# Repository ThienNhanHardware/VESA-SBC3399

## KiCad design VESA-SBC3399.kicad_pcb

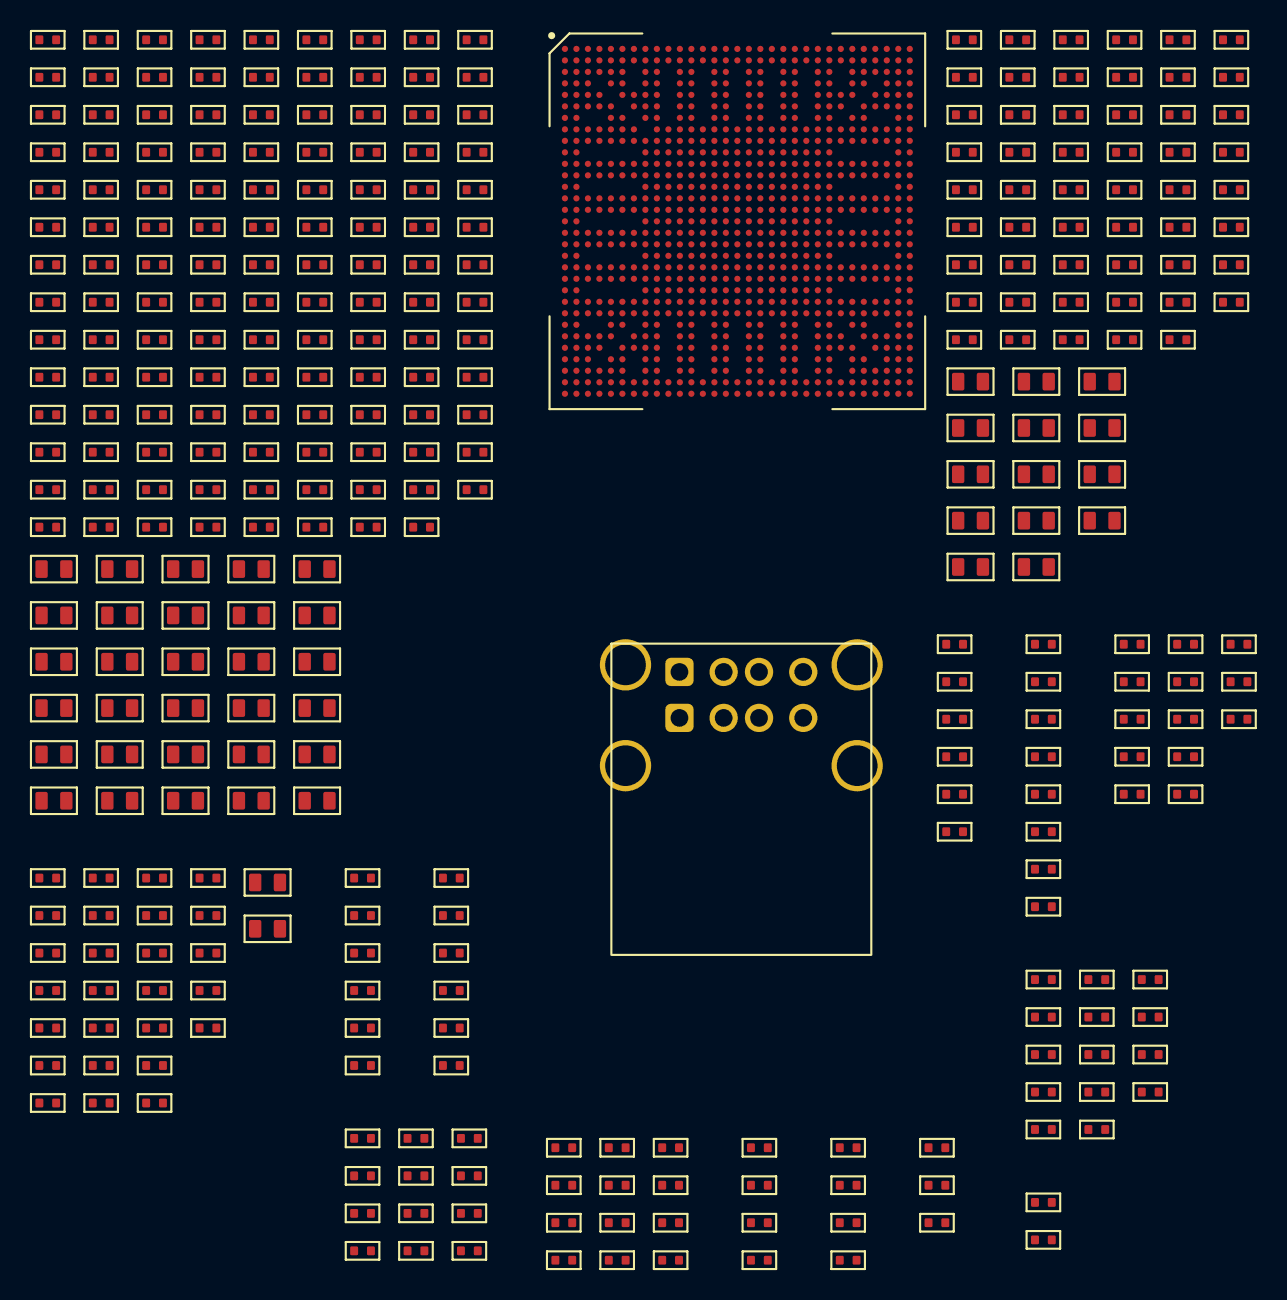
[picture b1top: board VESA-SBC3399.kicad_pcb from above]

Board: 2 copper layers, 342 parts (0 on the bottom side), 118 nets, no tracks yet.

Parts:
C2, C4, C7, C8, C9, C10, C14, C15, C16, C21, C23, C24, C28, C29, C30, C31, C32, C33, C34, C37, C38, C40, C41, C42, C47, C50, C51, C52, C53, C54, C56, C57, C58, C61, C62, C63, C67, C68, C69, C72, C73, C77, C78, C79, C80, C81, C82, C83, C84, C88, C89, C90, C91, C92, C94, C95, C98, C99, C100, C101, C102, C104, C105, C106, C107, C108, C109, C110, C111, C113, C114, C115, C116, C117, C118, C119, C122, C123, C124, C126, C127, C128, C129, C130, C131, C132, C136, C137, C138, C139, C140, C141, C142, C143, C146, C147, C148, C149, C150, C151, C152, C156, C157, C158, C159, C160, C161, C162, C163, C168, C170, C171, C172, C173, C174, C175, C176, C178, C179, C180, C181, C182, C183, C184, C185, C186, C187, C188, C189, C190, C191, C192, C193, C194, C195, C196, C197, C198, C199, C200, C201, C202, C203, C204, C205, C206, C207, C209, C210, C211, C212, C213, C214, C215, C216, C218, C219, C220, C221, C222, C223, C224, C225, C226, C227, C228, C229, C230, C231, C232, C233, C234, C235, C236, C237, C238, C239, C240, C241, C242, C243, C244, C245, C246, C247, C248: CAPC1005X50N
C13, C17, C18, C19, C20, C39, C43, C44, C45, C46, C49, C59, C60, C64, C65, C66, C70, C71, C74, C85, C86, C87, C93, C96, C97, C103, C112, C120, C121, C125, C133, C134, C135, C144, C145, C153, C154, C155, C164, C165, C166, C167, C169, C177, C208, C217: CAPC1608X80N
CON1: AF SS-JB17.6
R1, R2, R4, R5, R7, R9, R11, R12, R13, R14, R15, R17, R18, R21, R22, R23, R24, R25, R26, R27, R28, R29, R30, R31, R32, R33, R34, R35, R36, R37, R39, R40, R41, R43, R44, R45, R46, R47, R48, R50, R51, R52, R53, R55, R56, R57, R60, R61, R62, R63, R64, R65, R66, R67, R68, R69, R70, R71, R72, R73, R74, R75, R76, R77, R78, R79, R80, R81, R82, R83, R84, R85, R86, R87, R88, R89, R90, R93, R94, R95, R96, R97, R98, R99, R100, R101, R102, R103, R104, R105, R106, R107, R108, R109, R110, R111, R112, R113, R114, R115, R116, R117, R118, R119, R120, R121, R122, R123: RESC1005X35N
U11: RK3399; BGA828C65P31X31_2100X2100X161

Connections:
+0V9_AVCC: C108.1, C109.1, C110.1, C185.1, C186.1, C202.1, C204.1, C228.1, C231.1, C232.1, C233.1, C238.1, U11.H14 (DDR1PLL_AVDD_0V9), U11.L24 (EMMC_COREDLL_0V9), U11.R8 (DDR0PLL_AVDD_0V9), U11.R17 (PLL_AVDD_0V9), U11.T24 (PMU_VDD_0V9), U11.W24 (PCIE_AVDD_0V9), U11.Y18 (TYPEC0_AVDD_0V9_2), U11.Y19 (TYPEC0_AVDD_0V9_1), U11.Y21 (TYPEC1_AVDD_0V9_1), U11.Y22 (TYPEC1_AVDD_0V9_2)
+0V9_AVCC_HDMI: C96.1, U11.AA16 (HDMI_AVDD_0V9_1), U11.AA17 (HDMI_AVDD_0V9_2)
+0V9_VDD_CENTER: C70.1, C71.1, C72.1, C168.1, C169.1, C170.1, C171.1, C172.1, C173.1, C174.1, C175.1, R36.1, U11.M11 (CENTERLOGIC_VDD_1), U11.M12 (CENTERLOGIC_VDD_2), U11.M13 (CENTERLOGIC_VDD_3), U11.M14 (CENTERLOGIC_VDD_4), U11.M15 (CENTERLOGIC_VDD_5), U11.N11 (CENTERLOGIC_VDD_6), U11.N12 (CENTERLOGIC_VDD_7), U11.P13 (CENTERLOGIC_VDD_8), U11.P14 (CENTERLOGIC_VDD_9), U11.P15 (CENTERLOGIC_VDD_10)
+0V9_VDD_CPU_B: C15.1, C16.1, C17.1, C18.1, C19.1, C20.1, C132.1, C133.1, C134.1, C135.1, C136.1, C137.1, C138.1, C139.1, C140.1, C141.1, C142.1, R13.2, U11.K19 (BIGCPU_VDD_12), U11.K21 (BIGCPU_VDD_13), U11.L18 (BIGCPU_VDD_8), U11.L19 (BIGCPU_VDD_1), U11.L21 (BIGCPU_VDD_2), U11.L23 (BIGCPU_VDD_11), U11.M18 (BIGCPU_VDD_3), U11.M19 (BIGCPU_VDD_4), U11.M20 (BIGCPU_VDD_5), U11.M21 (BIGCPU_VDD_6), U11.M22 (BIGCPU_VDD_7), U11.N20 (BIGCPU_VDD_10), U11.N22 (BIGCPU_VDD_9)
+0V9_VDD_CPU_L: C86.1, C87.1, C88.1, C143.1, C144.1, C145.1, C146.1, C147.1, C148.1, C149.1, C150.1, C151.1, R39.1, U11.P20 (LITCPU_VDD_1), U11.P22 (LITCPU_VDD_4), U11.R19 (LITCPU_VDD_2), U11.R20 (LITCPU_VDD_3), U11.R22 (LITCPU_VDD_7), U11.T20 (LITCPU_VDD_6), U11.T22 (LITCPU_VDD_5)
+0V9_VDD_GPU: C41.1, C42.1, C43.1, C44.1, C45.1, C46.1, C152.1, C153.1, C154.1, C155.1, C156.1, C157.1, C158.1, C159.1, C160.1, C161.1, C162.1, C163.1, C164.1, C165.1, C166.1, C167.1, R26.2, U11.R11 (GPU_VDD_8), U11.R12 (GPU_VDD_9), U11.R13 (GPU_VDD_13), U11.T11 (GPU_VDD_10), U11.T12 (GPU_VDD_11), U11.T13 (GPU_VDD_12), U11.T14 (GPU_VDD_14), U11.U13 (GPU_VDD_7), U11.V11 (GPU_VDD_15), U11.V12 (GPU_VDD_16), U11.V13 (GPU_VDD_6), U11.V14 (GPU_VDD_5), U11.V15 (GPU_VDD_4), U11.V16 (GPU_VDD_17), U11.W10 (GPU_VDD_20), U11.W11 (GPU_VDD_1), U11.W12 (GPU_VDD_2), U11.W14 (GPU_VDD_3), U11.W15 (GPU_VDD_19), U11.W16 (GPU_VDD_18)
+0V9_VDD_LOG: C123.1, C124.1, C125.1, C128.1, C176.1, C177.1, C178.1, C179.1, C180.1, C181.1, C182.1, C183.1, C184.1, R50.1, R50.2, R53.1, U11.L17 (LOGIC_VDD_10), U11.M17 (LOGIC_VDD_9), U11.T17 (LOGIC_VDD_11), U11.U17 (LOGIC_VDD_8), U11.U18 (LOGIC_VDD_7), U11.U20 (LOGIC_VDD_12), U11.V18 (LOGIC_VDD_5), U11.V19 (LOGIC_VDD_4), U11.V20 (LOGIC_VDD_3), U11.V21 (LOGIC_VDD_2), U11.V22 (LOGIC_VDD_1), U11.W20 (LOGIC_VDD_6)
+1V5_VCC: C101.1, C196.1, R61.1, U11.AC8 (APIO4_VDDPST)
+1V8_AVCC: C94.1, C187.1, C188.1, C189.1, C234.1, C235.1, C239.1, C242.1, C244.1, C245.1, R67.1, R93.1, R95.1, U11.AA18 (TYPEC0_AVDD_1V8), U11.AA21 (TYPEC1_AVDD_1V8), U11.AC24 (ADC_AVDD), U11.P18 (PLL_AVDD_1V8), U11.R24 (PMUIO1_VDD_1V8), U11.U25 (PMU_VDD_1V8)
+1V8_AVCC_HDMI: C93.1, C246.1, C247.1, U11.AD16 (HDMI_AVDD_1V8)
+1V8_VCC: C73.1, C74.1, C115.1, C190.1, C192.1, C193.1, C194.1, C203.1, C205.1, R14.1, R27.1, R46.1, R47.1, R52.1, R60.1, R118.1, R119.1, R120.1, R121.1, R122.1, R123.1, U11.AA8 (APIO5_VDDPST), U11.AB8 (APIO3_VDD_1V8), U11.J22 (APIO1_VDDPST), U11.K24 (EMMC_VDD_1V8), U11.N23 (PMUIO2_VDDPST), U11.P23 (PMUIO2_VDD), U11.Y8 (APIO5_VDD), U11.Y24 (PCIE_AVDD_1V8)
+1V8_VCC_EFUSE: C201.1, R66.1, U11.AD23 (EFUSE)
+1V35_VCC_DDR: C82.1, C83.1, C84.1, C85.1, C208.1, C209.1, C210.1, C211.1, C212.1, C213.1, C214.1, C215.1, C216.1, C217.1, C218.1, C219.1, C220.1, C221.1, C222.1, C223.1, C224.1, C225.1, C226.1, C229.1, R37.1, R85.1, R86.1, U11.J11 (DDR1_VDD_1), U11.J12 (DDR1_VDD_2), U11.J13 (DDR1_VDD_3), U11.J14 (DDR1_VDD_4), U11.J15 (DDR1_VDD_5), U11.J16 (DDR1_VDD_6), U11.J17 (DDR1_VDD_7), U11.J18 (DDR1_VDD_8), U11.K11 (DDR1_VDD_9), U11.K13 (DDR1_VDD_10), U11.K15 (DDR1_VDD_11), U11.K17 (DDR1_VDD_12), U11.L9 (DDR0_VDD_1), U11.L10 (DDR0_VDD_2), U11.M9 (DDR0_VDD_3), U11.N9 (DDR0_VDD_4), U11.N10 (DDR0_VDD_5), U11.P9 (DDR0_VDD_6), U11.R9 (DDR0_VDD_7), U11.R10 (DDR0_VDD_8), U11.T9 (DDR0_VDD_9), U11.U9 (DDR0_VDD_10), U11.U10 (DDR0_VDD_11), U11.V9 (DDR0_VDD_12)
+1V35_VCC_DDR0_CLK: C227.1, R85.2, U11.M7 (DDR0_CLK_VDD)
+1V35_VCC_DDR1_CLK: C230.1, R86.2, U11.G12 (DDR1_CLK_VDD)
+3V0_IOVCC_SD: C97.1, C206.1, U11.T23 (SDMMC0_VDD)
+3V0_SDMMC0_VDDPST: C207.1, U11.U26 (SDMMC0_VDDPST)
+3V0_VCC: C103.1, C195.1, U11.AC9 (APIO4_VDD)
+3V0_VCC_RTC: C113.1, C114.1, R43.1, R48.1
+3V0_VCC_SD: C79.1, C80.1, C81.1
+3V3_VCC_LAN: C191.1, R107.1, R108.1, R109.1, R110.1, R111.1, U11.J23 (APIO1_VDD)
+3V3_VCC_SYS: C62.1, C63.1, C64.1, C65.1, C66.1, C77.1, C78.1, C106.1, C107.1, C111.1, C236.1, C237.1, C240.1, R33.1, R41.1, U11.AB18 (TYPEC0_AVDD_3V3), U11.AB21 (TYPEC1_AVDD_3V3), U11.Y25 (USB_AVDD_3V3)
+5V0_SYS: C13.1, C14.1, C39.1, C40.1, C52.1, C53.1, C54.1, C59.1, C60.1, C61.1, C68.1, C69.1, C90.1, C92.1, C95.1, C98.1, C100.1, C102.1, C120.1, C121.1, C122.1, R29.1
+5V0_USB: C32.1, C33.1, C34.1
+5V0_VBUS_USBA0: C2.1, CON1.1 (VBUS1)
+5V0_VBUS_USBA1: C4.1, CON1.5 (VBUS2)
+12V_SYS: C8.1, C9.1, C10.1, C28.1, C29.1, C30.1, C31.1, C49.1, C50.1, R7.1, R28.1
/0V9_VDD_CPU_B_FB: R13.1, U11.N18 (BIGCPU_VDD_COM)
/0V9_VDD_GPU_FB: R26.1, U11.T15 (GPU_VDD_COM)
/BT_REG_ON: R67.2, R68.1, U11.V30 (GPIO0_B1/PMUIO2_VOLSEL)
/CPU-RK3399/CPU-RK3399 HDMI/HDMI_TMDS0_R+: R98.1, U11.AK17 (HDMI_TX0P)
/CPU-RK3399/CPU-RK3399 HDMI/HDMI_TMDS0_R-: R99.1, U11.AL17 (HDMI_TX0N)
/CPU-RK3399/CPU-RK3399 HDMI/HDMI_TMDS1_R+: R100.1, U11.AK18 (HDMI_TX1P)
/CPU-RK3399/CPU-RK3399 HDMI/HDMI_TMDS1_R-: R101.1, U11.AL18 (HDMI_TX1N)
/CPU-RK3399/CPU-RK3399 HDMI/HDMI_TMDS2_R+: R103.1, U11.AK19 (HDMI_TX2P)
/CPU-RK3399/CPU-RK3399 HDMI/HDMI_TMDS2_R-: R104.1, U11.AL19 (HDMI_TX2N)
/CPU-RK3399/CPU-RK3399 HDMI/HDMI_TMDS_CLK_R+: R97.1, U11.AK16 (HDMI_TCP)
/CPU-RK3399/CPU-RK3399 HDMI/HDMI_TMDS_CLK_R-: R102.1, U11.AL16 (HDMI_TCN)
/CPU-RK3399/CPU-RK3399 PMU Controller/CPU_SYS_CLK32K_IN: C199.1, R62.1, U11.U31 (GPIO0_A0/TEST_CLKOUT0/CLK32K_IN)
/CPU-RK3399/CPU-RK3399 PMU Controller/CPU_XIN_OSC: C198.1, R63.1, U11.Y31 (XIN_OSC)
/CPU-RK3399/CPU-RK3399 PMU Controller/CPU_XOUT_OSC: R63.2, R64.2, U11.Y30 (XOUT_OSC)
/CPU-RK3399/CPU-RK3399 Protocols/CPU_I2C0_SCL: R122.2, U11.N30 (GPIO1_C0/SPI3_TXD/I2C0_SCL)
/CPU-RK3399/CPU-RK3399 Protocols/CPU_I2C0_SDA: R123.2, U11.M26 (GPIO1_B7/SPI3_RXD/I2C0_SDA)
/CPU-RK3399/CPU-RK3399 Protocols/CPU_I2C3_SCL: R119.2, U11.AL2 (GPIO4_C1/I2C3_SCL/UART2B_TX)
/CPU-RK3399/CPU-RK3399 Protocols/CPU_I2C3_SDA: R118.2, U11.AG6 (GPIO4_C0/I2C3_SDA/UART2B_RX)
/CPU-RK3399/CPU-RK3399 Protocols/CPU_I2C4_SCL: R120.2, U11.P30 (GPIO1_B4/I2C4_SCL)
/CPU-RK3399/CPU-RK3399 Protocols/CPU_I2C4_SDA: R121.2, U11.P31 (GPIO1_B3/I2C4_SDA)
/CPU-RK3399/CPU-RK3399 SAR-ADC/CPU_SYS_RAM_ID: C241.1, R93.2, R94.1, U11.AG28 (ADC_IN3)
/CPU_SYS_RECOVERY: C243.1, R95.2, R96.2, U11.AH26 (ADC_IN1)
/CPU_SYS_RESET#: C119.1, C197.1, R47.2, U11.T30 (NPOR)
/PHY_CLKOUT: C248.1, R117.2
/PHY_MDIO: R107.2, U11.G26 (GPIO3_B5/MAC_MDIO/UART1_TX)
/PHY_TXD0: R111.2, R112.2
/PHY_TXD1: R110.2, R113.2
/PHY_TXD2: R109.2, R114.2
/PHY_TXD3: R108.2, R115.2
/PMIC_PWR_KEY#: C130.1, R48.2, U11.V27 (GPIO0_A5/EMMC_PWRON)
/PMIC_RTC_CLKO_CPU: R46.2, R62.2
/Power/0V9_VDD_CPU_B_PWR_EN: C23.1, R14.2
/Power/0V9_VDD_GPU_PWR_EN: C51.1, R27.2
/Power/0V9_VDD_LOG_FB: C128.2, R53.2, R55.2, R57.1
/Power/1V35_VCC_DDR_FB: C82.2, R40.1
/Power/3V3_VCC_SYS_FB: R33.2, R34.1
/Power/3V3_VCC_SYS_PWR_EN: C67.1, R35.2
/Power/5V0_SYS_FB: R29.2, R31.1
/Power/5V0_SYS_PWR_EN: R18.2, R28.2, R30.1
/Power/5V0_USB_PWR_EN: R17.2, R21.1
/Power/12V_SYS_OVLO: R9.2, R15.1
/Power/12V_SYS_PG: R12.2, R17.1, R18.1
/USB 2.0 Type-A/USBA0_D_R+: CON1.3 (D1+), R1.2
/USB 2.0 Type-A/USBA0_D_R-: CON1.2 (D1-), R2.2
/USB 2.0 Type-A/USBA1_D_R+: CON1.7 (D2+), R4.2
/USB 2.0 Type-A/USBA1_D_R-: CON1.6 (D2-), R5.2
/USBA0_D+: R1.1, U11.AB30 (USB0_DP)
/USBA0_D-: R2.1, U11.AB31 (USB0_DN)
/USBA1_D+: R4.1, U11.AA30 (USB1_DP)
/USBA1_D-: R5.1, U11.AA31 (USB1_DN)
CHGND: CON1.9 (SHIELD), CON1.10 (SHIELD), CON1.11 (SHIELD), CON1.12 (SHIELD)
GND: C2.2, C4.2, C7.2, C8.2, C9.2, C10.2, C13.2, C14.2, C15.2, C16.2, C17.2, C18.2, C19.2, C20.2, C21.2, C23.2, C28.2, C29.2, C30.2, C31.2, C32.2, C33.2, C34.2, C37.2, C38.2, C39.2, C40.2, C41.2, C42.2, C43.2, C44.2, C45.2, C46.2, C49.2, C50.2, C51.2, C52.2, C53.2, C54.2, C56.2, C57.2, C59.2, C60.2, C61.2, C62.2, C63.2, C64.2, C65.2, C66.2, C67.2, C68.2, C69.2, C70.2, C71.2, C72.2, C73.2, C74.2, C77.2, C78.2, C79.2, C80.2, C81.2, C83.2, C84.2, C85.2, C86.2, C87.2, C88.2, C89.2, C90.2, C91.2, C92.2, C93.2, C94.2, C95.2, C96.2, C97.2, C98.2, C99.2, C100.2, C101.2, C102.2, C103.2, C104.2, C105.2, C106.2, C107.2, C108.2, C109.2, C110.2, C111.2, C112.2, C113.2, C114.2, C115.2, C116.2, C117.2, C118.2, C119.2, C121.2, C122.2, C123.2, C124.2, C125.2, C126.2, C127.2, C129.2, C130.2, C131.2, C132.2, C133.2, C134.2, C135.2, C136.2, C137.2, C138.2, C139.2, C140.2, C141.2, C142.2, C143.2, C144.2, C145.2, C146.2, C147.2, C148.2, C149.2, C150.2, C151.2, C152.2, C153.2, C154.2, C155.2, C156.2, C157.2, C158.2, C159.2, C160.2, C161.2, C162.2, C163.2, C164.2, C165.2, C166.2, C167.2, C168.2, C169.2, C170.2, C171.2, C172.2, C173.2, C174.2, C175.2, C176.2, C177.2, C178.2, C179.2, C180.2, C181.2, C182.2, C183.2, C184.2, C185.2, C186.2, C187.2, C188.2, C189.2, C190.2, C191.2, C192.2, C193.2, C194.2, C195.2, C196.2, C197.2, C198.2, C199.2, C200.2, C201.2, C202.2, C203.2, C204.2, C205.2, C206.2, C207.2, C208.2, C209.2, C210.2, C211.2, C212.2, C213.2, C214.2, C215.2, C216.2, C217.2, C218.2, C219.2, C220.2, C221.2, C222.2, C223.2, C224.2, C225.2, C226.2, C227.2, C228.2, C229.2, C230.2, C231.2, C232.2, C233.2, C234.2, C235.2, C236.2, C237.2, C238.2, C239.2, C240.2, C241.2, C242.2, C243.2, C244.2, C245.2, C246.2, C247.2, C248.2, CON1.4 (GND1), CON1.8 (GND2), R11.2, R15.2, R21.2, R22.2, R23.2, R24.2, R30.2, R31.2, R34.2, R45.2, R51.2, R56.2, R57.2, R60.2, R61.2, R66.2, R68.2, R76.2, R83.2, R84.2, R87.2, R88.2, R89.2, R90.2, R94.2, R106.2, U11.A1 (VSS_1), U11.A27 (VSS_2), U11.A31 (VSS_3), U11.AA3 (VSS_4), U11.AA5 (VSS_5), U11.AA9 (VSS_6), U11.AA10 (VSS_179), U11.AA11 (AVSS_13), U11.AA12 (AVSS_17), U11.AA13 (VSS_177), U11.AA14 (AVSS_26), U11.AA15 (AVSS_53), U11.AA23 (AVSS_4), U11.AA26 (AVSS_6), U11.AA29 (AVSS_7), U11.AB9 (VSS_9), U11.AB10 (AVSS_12), U11.AB11 (AVSS_8), U11.AB13 (AVSS_9), U11.AB15 (AVSS_42), U11.AB16 (AVSS_41), U11.AB17 (AVSS_52), U11.AB19 (VSS_140), U11.AB23 (AVSS_5), U11.AC3 (VSS_16), U11.AC11 (AVSS_44), U11.AC13 (AVSS_45), U11.AC15 (AVSS_10), U11.AC16 (AVSS_18), U11.AC17 (AVSS_43), U11.AC18 (VSS_145), U11.AC20 (VSS_13), U11.AC21 (VSS_132), U11.AC22 (VSS_12), U11.AC23 (AVSS_19), U11.AC25 (AVSS_51), U11.AC26 (AVSS_14), U11.AC29 (AVSS_15), U11.AD3 (VSS_17), U11.AD5 (VSS_18), U11.AD10 (VSS_19), U11.AD13 (AVSS_11), U11.AD17 (AVSS_16), U11.AD21 (VSS_163), U11.AD22 (VSS_11), U11.AD26 (AVSS_40), U11.AD29 (AVSS_20), U11.AE11 (AVSS_21), U11.AE12 (AVSS_22), U11.AE14 (AVSS_23), U11.AE17 (AVSS_24), U11.AE23 (VSS_14), U11.AE27 (AVSS_25), U11.AF9 (VSS_20), U11.AF17 (AVSS_27), U11.AF18 (VSS_7), U11.AF20 (VSS_10), U11.AF23 (AVSS_2), U11.AF24 (AVSS_3), U11.AF29 (AVSS_28), U11.AG2 (VSS_21), U11.AG29 (AVSS_29), U11.AH29 (AVSS_30), U11.AJ5 (VSS_22), U11.AJ6 (AVSS_31), U11.AJ8 (AVSS_32), U11.AJ9 (AVSS_33), U11.AJ11 (AVSS_34), U11.AJ12 (AVSS_35), U11.AJ14 (AVSS_36), U11.AJ15 (AVSS_37), U11.AJ17 (AVSS_38), U11.AJ18 (AVSS_39), U11.AJ20 (VSS_180), U11.AJ21 (VSS_172), U11.AJ23 (VSS_173), U11.AJ24 (VSS_174), U11.AJ26 (VSS_175), U11.AJ27 (VSS_176), U11.AJ28 (VSS_171), U11.AJ29 (AVSS_47), U11.AL1 (VSS_23), U11.AL31 (VSS_178), U11.B5 (VSS_24), U11.B31 (EDP_AVSS_1), U11.C8 (VSS_25), U11.C9 (VSS_26), U11.C11 (VSS_27), U11.C12 (VSS_28), U11.C14 (VSS_29), U11.C15 (VSS_30), U11.C17 (VSS_31), U11.C18 (VSS_32), U11.C20 (VSS_33), U11.C21 (VSS_34), U11.C23 (VSS_35), U11.C24 (VSS_36), U11.C26 (VSS_37), U11.C28 (EDP_AVSS_2), U11.C29 (EDP_AVSS_3), U11.D5 (VSS_38), U11.D29 (EDP_AVSS_4), U11.E2 (VSS_39), U11.E4 (VSS_40), U11.E7 (VSS_41), U11.E12 (VSS_42), U11.E15 (VSS_43), U11.E18 (VSS_44), U11.E21 (VSS_45), U11.E24 (VSS_46), U11.E31 (VSS_47), U11.F8 (VSS_48), U11.F15 (VSS_49), U11.F18 (VSS_50), U11.F20 (VSS_51), U11.F21 (VSS_52), U11.G5 (VSS_53), U11.G9 (VSS_54), U11.G18 (VSS_55), U11.G27 (VSS_56), U11.H3 (VSS_57), U11.H9 (VSS_58), U11.H10 (VSS_59), U11.H11 (VSS_60), U11.H12 (VSS_61), U11.H13 (VSS_62), U11.H15 (VSS_63), U11.H16 (VSS_64), U11.H17 (VSS_65), U11.H18 (VSS_66), U11.H19 (EDP_AVSS_5), U11.H26 (VSS_67), U11.J3 (VSS_68), U11.J6 (VSS_69), U11.J7 (VSS_70), U11.J8 (VSS_71), U11.J9 (VSS_72), U11.J10 (VSS_73), U11.J21 (EDP_AVSS_6), U11.K8 (VSS_74), U11.K9 (VSS_75), U11.K10 (VSS_76), U11.K12 (VSS_77), U11.K14 (VSS_78), U11.K16 (VSS_79), U11.K18 (VSS_80), U11.K20 (VSS_82), U11.K22 (VSS_84), U11.L3 (VSS_85), U11.L6 (VSS_86), U11.L8 (VSS_87), U11.L11 (VSS_88), U11.L12 (VSS_89), U11.L13 (VSS_90), U11.L14 (VSS_91), U11.L15 (VSS_92), U11.L16 (VSS_93), U11.L20 (VSS_96), U11.L22 (VSS_97), U11.L27 (VSS_99), U11.M3 (VSS_100), U11.M8 (VSS_101), U11.M10 (VSS_102), U11.M16 (VSS_103), U11.M23 (VSS_104), U11.N8 (VSS_105), U11.N13 (VSS_108), U11.N14 (VSS_109), U11.N15 (VSS_110), U11.N16 (VSS_111), U11.N17 (VSS_94), U11.N19 (VSS_83), U11.N21 (VSS_98), U11.P3 (VSS_112), U11.P6 (VSS_113), U11.P7 (VSS_114), U11.P8 (VSS_115), U11.P10 (VSS_116), U11.P11 (VSS_106), U11.P12 (VSS_107), U11.P16 (VSS_117), U11.P17 (PLL_AVSS), U11.P19 (VSS_119), U11.P21 (VSS_121), U11.R3 (VSS_123), U11.R5 (VSS_124), U11.R6 (VSS_125), U11.R14 (VSS_129), U11.R15 (VSS_130), U11.R16 (VSS_131), U11.R18 (VSS_165), U11.R21 (VSS_120), U11.R23 (VSS_133), U11.T8 (VSS_134), U11.T10 (VSS_135), U11.T16 (VSS_138), U11.T18 (VSS_168), U11.T19 (VSS_122), U11.T21 (VSS_139), U11.U3 (VSS_141), U11.U8 (VSS_142), U11.U11 (VSS_126), U11.U12 (VSS_127), U11.U14 (VSS_137), U11.U15 (VSS_143), U11.U16 (VSS_144), U11.U19 (VSS_146), U11.U21 (VSS_147), U11.U22 (VSS_149), U11.U23 (AVSS_49), U11.U29 (VSS_150), U11.V3 (VSS_151), U11.V5 (VSS_152), U11.V8 (VSS_153), U11.V10 (VSS_154), U11.V17 (VSS_148), U11.V23 (AVSS_50), U11.W8 (VSS_161), U11.W9 (VSS_162), U11.W13 (VSS_128), U11.W17 (VSS_159), U11.W18 (VSS_169), U11.W19 (VSS_167), U11.W21 (VSS_81), U11.W22 (VSS_158), U11.W23 (AVSS_46), U11.W30 (VSS_160), U11.Y3 (VSS_8), U11.Y9 (VSS_166), U11.Y10 (VSS_15), U11.Y11 (VSS_155), U11.Y12 (VSS_136), U11.Y13 (VSS_164), U11.Y14 (VSS_156), U11.Y15 (VSS_157), U11.Y16 (VSS_118), U11.Y17 (VSS_95), U11.Y20 (VSS_170), U11.Y23 (AVSS_1), U11.Y29 (AVSS_48)
unnamed: C131.1, R55.1, R56.1
unnamed: C200.1, R64.1
unnamed: C117.1, R44.2
unnamed: R44.1, R45.1
unnamed: R65.1, U11.M31 (GPIO1_C7/TCPD_VBUS_SOURCE1)
unnamed: R11.1, R12.1
unnamed: R37.2, R40.2
unnamed: C38.1, R25.2
unnamed: C56.1, R32.1
unnamed: C126.1, R51.1
unnamed: C127.1, R52.2
unnamed: R83.1, U11.R7 (DDR0_PZQ)
unnamed: R84.1, U11.G15 (DDR1_PZQ)
unnamed: R78.1, U11.Y27 (GPIO4_B0/SDMMC0_D0/UART2A_RX)
unnamed: R79.1, U11.Y26 (GPIO4_B1/SDMMC0_D1/UART2A_TX)
unnamed: R80.1, U11.Y28 (GPIO4_B2/SDMMC0_D2/APJTAG_TCK)
unnamed: R81.1, U11.U27 (GPIO4_B3/SDMMC0_D3/APJTAG_TMS)
unnamed: R77.1, U11.V29 (GPIO4_B4/SDMMC0_CLKOUT/MUCJTAG_TCK)
unnamed: R82.1, U11.V25 (GPIO4_B5/SDMMC0_CMD/MCUJTAG_TMS)
unnamed: R69.1, U11.AD8 (GPIO2_C4/SDIO0_D0/SPI5_RXD)
unnamed: R70.1, U11.AK5 (GPIO2_C5/SDIO0_D1/SPI5_TXD)
unnamed: R71.1, U11.AG7 (GPIO2_C6/SDIO0_D2/SPI5_CLK)
unnamed: R72.1, U11.AE8 (GPIO2_C7/SDIO0_D3/SPI5_CSN0)
unnamed: R73.1, U11.AH6 (GPIO2_D0/SDIO0_CMD)
unnamed: R74.1, U11.AF7 (GPIO2_D1/SDIO0_CLKOUT/TEST_CLKOUT1)
unnamed: R76.1, U11.L29 (EMMC_CALIO)
unnamed: R75.1, U11.L28 (EMMC_CLK)
unnamed: R89.1, U11.AC31 (USB0_RBIAS)
unnamed: R90.1, U11.AC30 (USB1_RBIAS)
unnamed: R87.1, U11.AG18 (TYPEC0_REXT)
unnamed: R88.1, U11.AE21 (TYPEC1_REXT)
unnamed: R105.1, U11.AE15 (HDMI_HPD)
unnamed: R106.1, U11.AF15 (HDMI_REXT)
unnamed: R114.1, U11.F24 (GPIO3_A0/MAC_TXD2/SPI4_RXD)
unnamed: R115.1, U11.H23 (GPIO3_A1/MAC_TXD3/SPI4_TXD)
unnamed: R112.1, U11.D26 (GPIO3_A4/MAC_TXD0/SPI0_RXD)
unnamed: R113.1, U11.G23 (GPIO3_A5/MAC_TXD1/SPI0_TXD)
unnamed: R117.1, U11.G24 (GPIO3_B3/MAC_CLK/I2C5_SCL)
unnamed: R116.1, U11.H22 (GPIO3_B4/MAC_TXEN/UART1_RX)

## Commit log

2026-01-09 generate schematic
2026-01-10 update schematic
2026-01-10 update root schematic
2026-01-10 create netclass
2026-01-11 design CPU Power
2026-01-12 update RK3399 power
2026-01-14 design CPU DDR
2026-01-14 design CPU-RK3399 eMMC Controller
2026-01-14 design CPU-RK3399 SDMMC
2026-01-14 design USB
2026-01-18 design PMIC
2026-01-20 update design power
2026-01-21 finish design power
2026-01-21 design USB-A
2026-01-27 design DDR
